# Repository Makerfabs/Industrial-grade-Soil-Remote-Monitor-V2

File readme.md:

# Makerfas Industrial-grade Soil Remote Monitor V2

```c++
/*
Version:		V1.1
Author:			Vincent
Create Date:	2023/7/25
Note:

*/
```

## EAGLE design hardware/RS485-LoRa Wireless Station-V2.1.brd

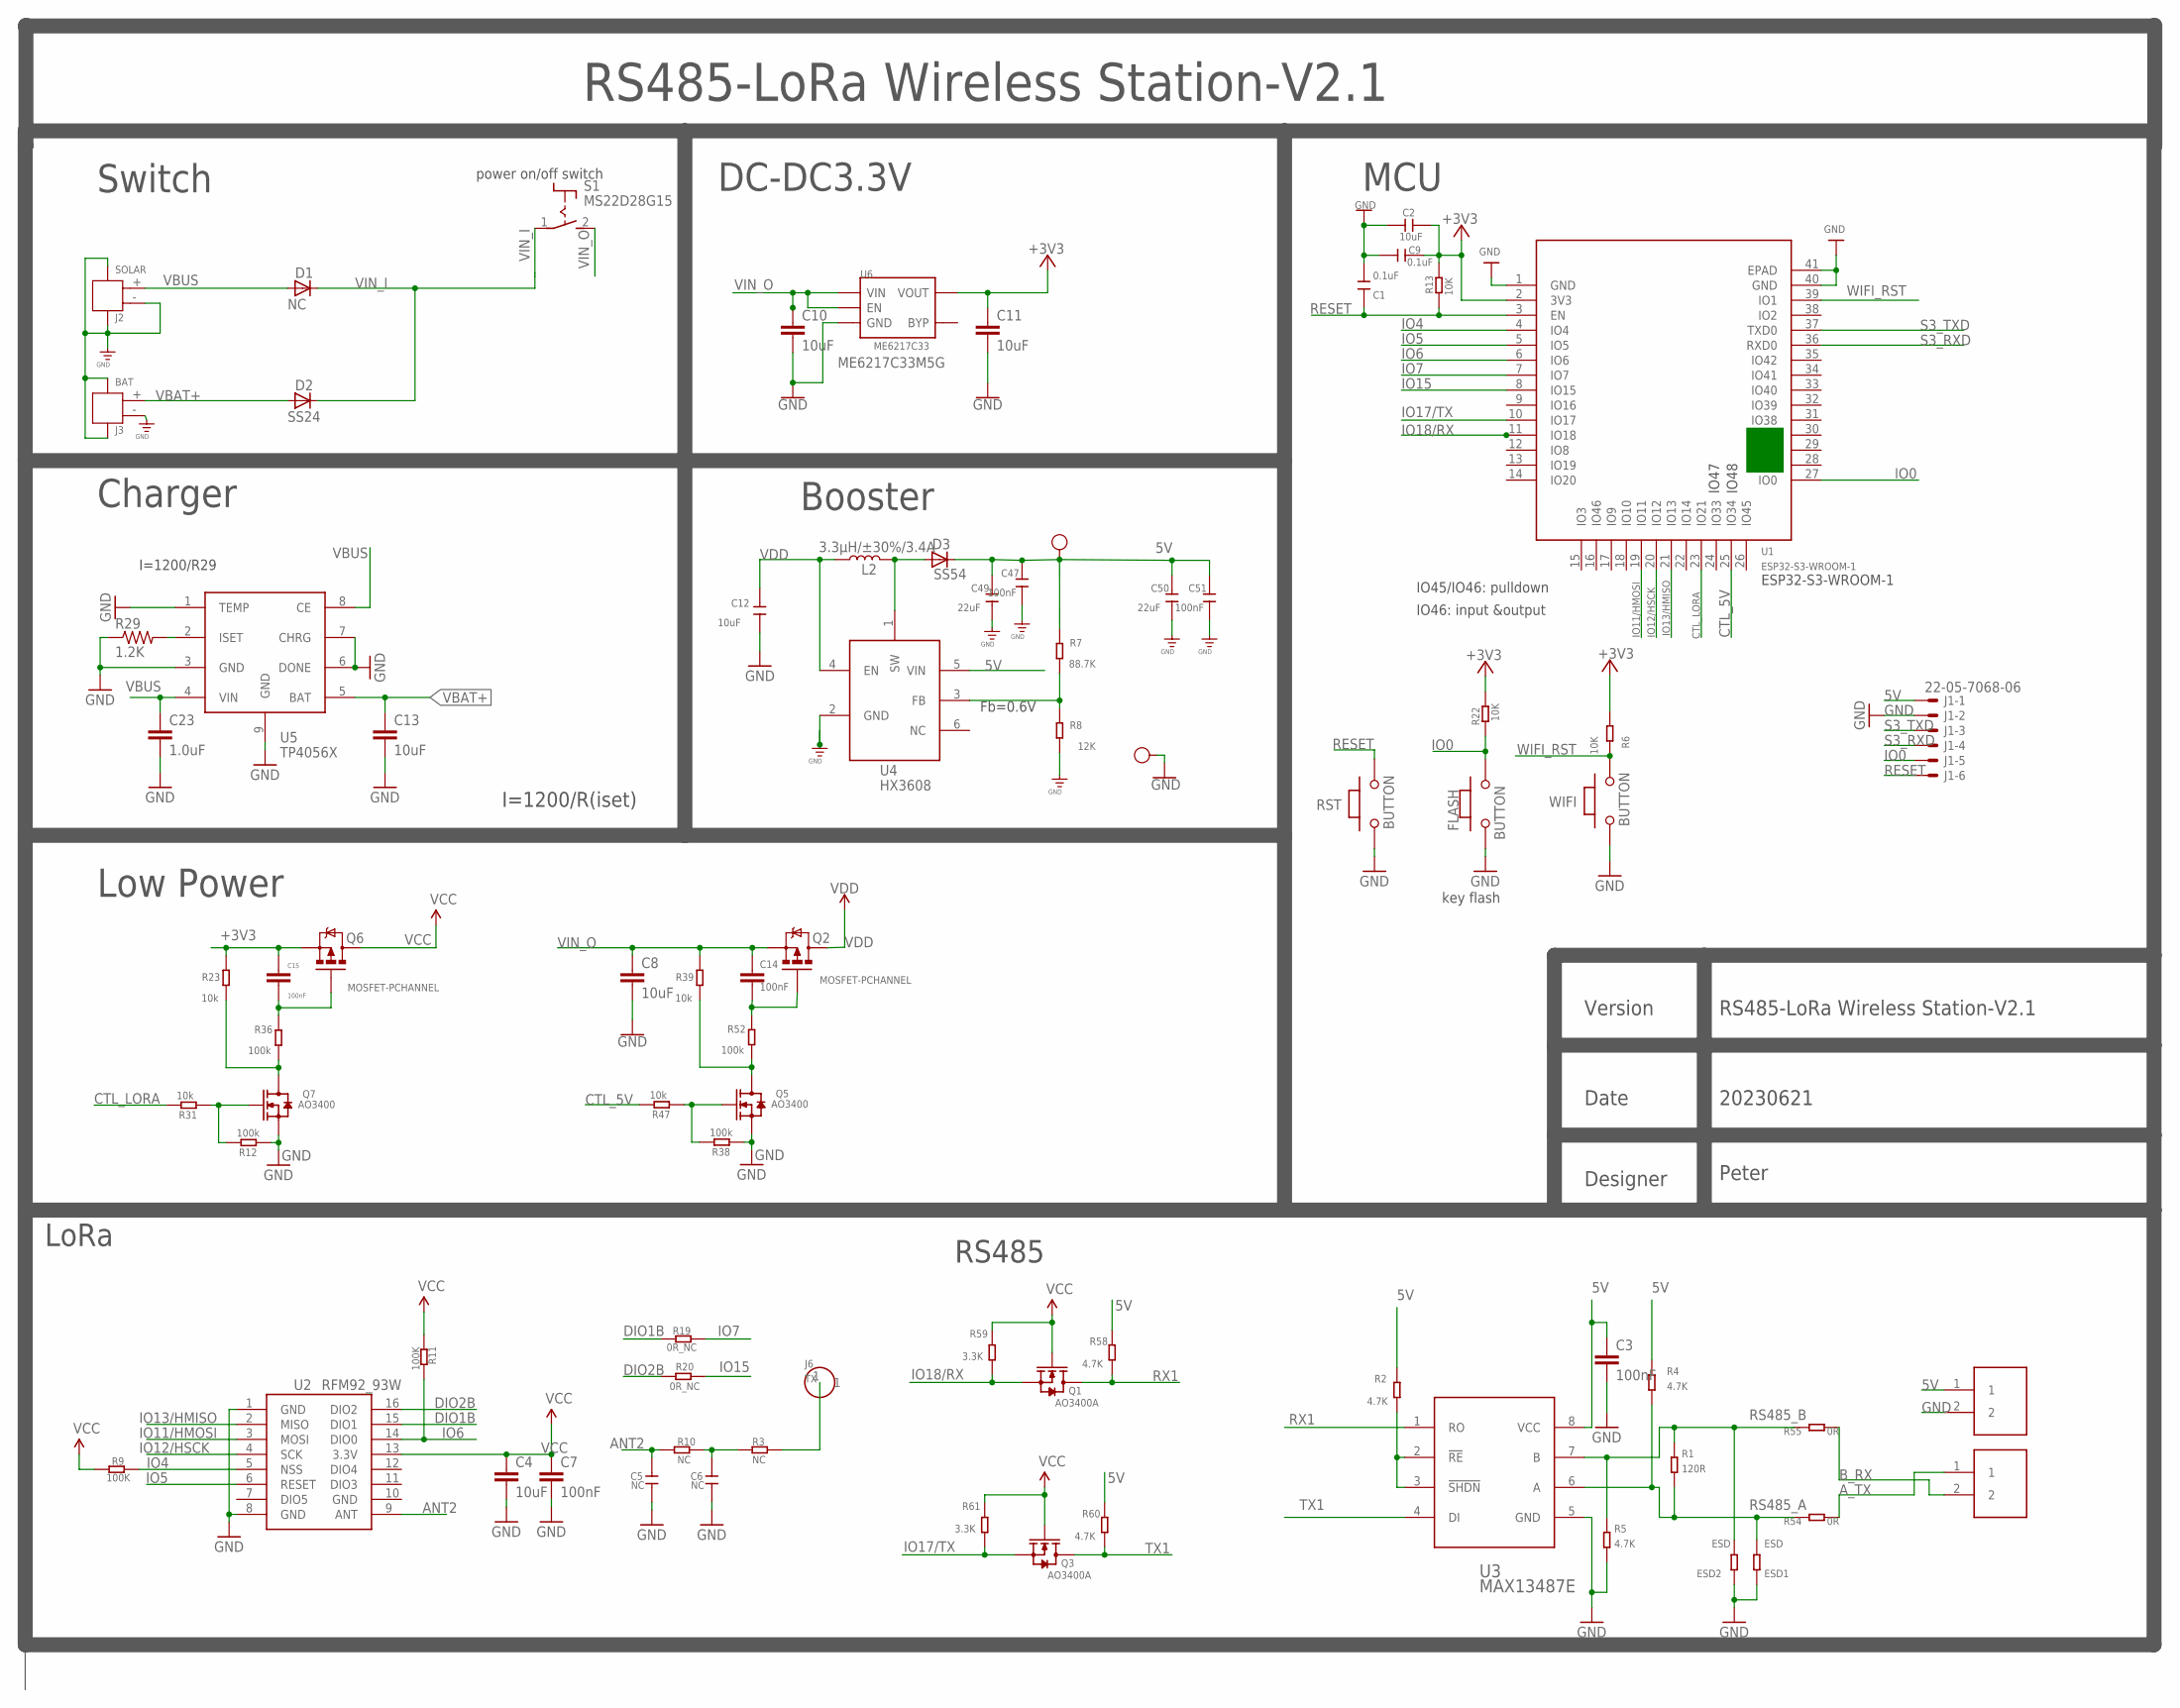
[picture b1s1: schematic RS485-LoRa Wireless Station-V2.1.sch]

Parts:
5V: HP; TP-D45MIL
C1, C9: 0.1uF; DISCRETE_C0603
C2: 10uF; DISCRETE_C0603
C3, C7, C14, C15, C47, C51: 100nF; C0603
C4, C8, C10, C11, C12, C13: 10uF; C0603
C5, C6: NC; DISCRETE_C0603
C23: 1.0uF; C0603
C49, C50: 22uF; C0603
D1: NC; DO-214AC
D2: SS24; DO-214AC
D3: SS54; DO-214AC
ESD1, ESD2: ESD; R0603
FLASH: BUTTON; 157SW
GND: HP; TP-D45MIL
J1: 22-05-7068-06; 7395-06
J2: SOLAR; HW2-SMD-2.0-90D
J3: BAT; HW2-SMD-2.0-90D
J4, J5: PH2.0-2P-DIP; PH2.0*2-DIP
J6: TX; 1P-100/50MIL
L2: 3.3µH/±30%/3.4A; CR54
Q1, Q3: AO3400A; SOT-23
Q2, Q6: MOSFET-PCHANNEL; SOT23-3
Q5, Q7: AO3400; SOT23@1
R1: 120R; R0603
R2, R4, R5, R58, R60: 4.7K; R0603
R3, R10: NC; DISCRETE_R0603
R6, R13, R22: 10K; R0603
R7: 88.7K; R0603
R8: 12K; R0603
R9, R11: 100K; R0603
R12, R36, R38, R52: 100k; R0603
R19, R20: 0R_NC; R0603
R23, R31, R39, R47: 10k; R0603
R29: 1.2K; R0603
R54, R55: 0R; R0603
R59, R61: 3.3K; R0603
RST: BUTTON; 157SW
S1: MS22D28G15; S-MS22D28G15
U1: ESP32-S3-WROOM-1; ESP32-­S2-­SOLO
U2: RFM92_93W
U3: MAX13487E; DIP8_MAX13487
U4: HX3608; SOT-23-6
U5: TP4056X; SOP8-1.27P
U6: ME6217C33; SOT23-5
WIFI: BUTTON; 157SW

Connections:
5V: 5V.T, C3.1, C47.1, C49.1, C50.1, C51.1, D3.C, J1.1, J4.1, R2.2, R4.2, R7.2, R58.2, R60.2, U3.8 (VCC), U4.5 (VIN)
+3V3: C2.1, C9.1, C11.1, C15.1, Q6.2 (S), R6.2, R13.2, R22.2, R23.2, U1.2 (3V3), U6.5 (VOUT)
ANT2: C5.2, R10.1, U2.9 (ANT)
A_TX: J5.1, R54.1
B_RX: J5.2, R55.1
CTL_5V: R47.2, U1.25 (IO34)
CTL_LORA: R31.2, U1.23 (IO21)
DIO1B: R19.2, U2.15 (DIO1)
DIO2B: R20.2, U2.16 (DIO2)
GND: C1.2, C2.2, C3.2, C4.2, C5.1, C6.1, C7.2, C8.2, C9.2, C10.2, C11.2, C12.2, C13.2, C23.2, C47.2, C49.2, C50.2, C51.2, ESD1.1, ESD2.1, FLASH.1, GND.T, J1.2, J2.3, J2.4, J2.- (2), J3.3, J3.4, J3.- (2), J4.2, Q5.2 (S), Q7.2 (S), R5.1, R8.1, R12.1, R29.1, R38.1, RST.1, U1.1 (GND), U1.40 (GND), U1.41 (EPAD), U2.1 (GND), U2.8 (GND), U2.10 (GND), U3.5 (GND), U4.2 (GND), U5.1 (TEMP), U5.3 (GND), U5.6 (DONE), U5.7 (CHRG), U5.9 (GND), U6.2 (GND), WIFI.1
IO0: FLASH.2, J1.5, R22.1, U1.27 (IO0)
IO4: R9.1, U1.4 (IO4), U2.5 (NSS)
IO5: U1.5 (IO5), U2.6 (RESET)
IO6: R11.1, U1.6 (IO6), U2.14 (DIO0)
IO7: R19.1, U1.7 (IO7)
IO11/HMOSI: U1.19 (IO11), U2.3 (MOSI)
IO12/HSCK: U1.20 (IO12), U2.4 (SCK)
IO13/HMISO: U1.21 (IO13), U2.2 (MISO)
IO15: R20.1, U1.8 (IO15)
IO17/TX: Q3.2 (S), R61.1, U1.10 (IO17)
IO18/RX: Q1.2 (S), R59.1, U1.11 (IO18)
ISET: R29.2, U5.2 (ISET)
unnamed: C6.2, R3.1, R10.2
unnamed: J6.1, R3.2
unnamed: C14.2, Q2.1 (G), R52.2
unnamed: Q5.1 (G), R38.2, R47.1
unnamed: C15.2, Q6.1 (G), R36.2
unnamed: Q7.1 (G), R12.2, R31.1
unnamed: Q7.3 (D), R23.1, R36.1
unnamed: D3.A, L2.P$2 (2), U4.1 (SW)
unnamed: R7.1, R8.2, U4.3 (FB)
unnamed: Q5.3 (D), R39.1, R52.1
unnamed: R2.1, U3.2 (!RE), U3.3 (!SHDN)
RESET: C1.1, J1.6, R13.1, RST.2, U1.3 (EN)
RS485_A: ESD1.2, R1.1, R4.1, R54.2, U3.6 (A)
RS485_B: ESD2.2, R1.2, R5.2, R55.2, U3.7 (B)
RX1: Q1.3 (D), R58.1, U3.1 (RO)
S3_RXD: J1.4, U1.36 (RXD0)
S3_TXD: J1.3, U1.37 (TXD0)
TX1: Q3.3 (D), R60.1, U3.4 (DI)
VBAT+: C13.1, D2.A, J3.+ (1), U5.5 (BAT)
VBUS: C23.1, D1.A, J2.+ (1), U5.4 (VIN), U5.8 (CE)
VCC: C4.1, C7.1, Q1.1 (G), Q3.1 (G), Q6.3 (D), R9.2, R11.2, R59.2, R61.2, U2.13 (3.3V)
VDD: C12.1, L2.P$1 (1), Q2.3 (D), U4.4 (EN)
VIN_I: D1.C, D2.C, S1.1
VIN_O: C8.1, C10.1, C14.1, Q2.2 (S), R39.2, S1.2 (S), U6.1 (VIN), U6.3 (EN)
WIFI_RST: R6.1, U1.39 (IO1), WIFI.2

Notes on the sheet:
DC-DC3.3V
I=1200/R29
ME6217C33M5G
Fb=0.6V
Charger
Booster
LoRa
RS485
power on/off switch
key flash
Switch
MCU
Low Power
IO45/IO46: pulldown
IO46: input &output
ESP32-S3-WROOM-1
IO47
IO48
I=1200/R(iset)
Version
Date
Designer
RS485-LoRa Wireless Station-V2.1
20230621
Peter

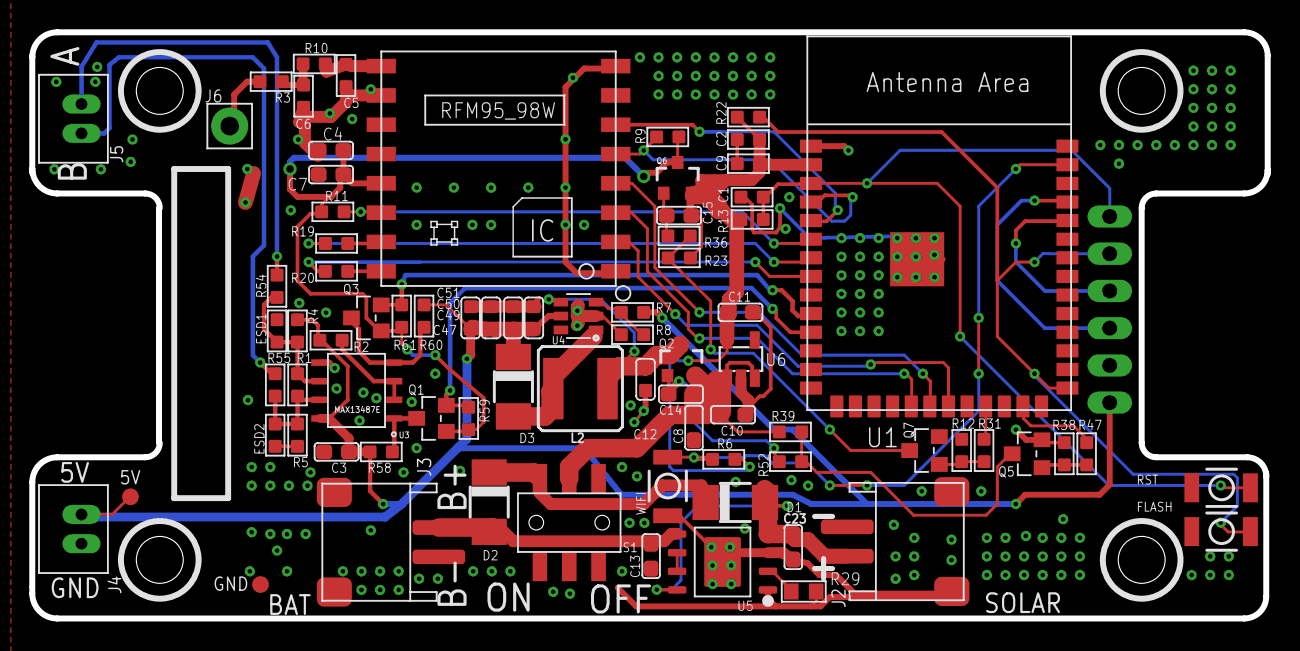
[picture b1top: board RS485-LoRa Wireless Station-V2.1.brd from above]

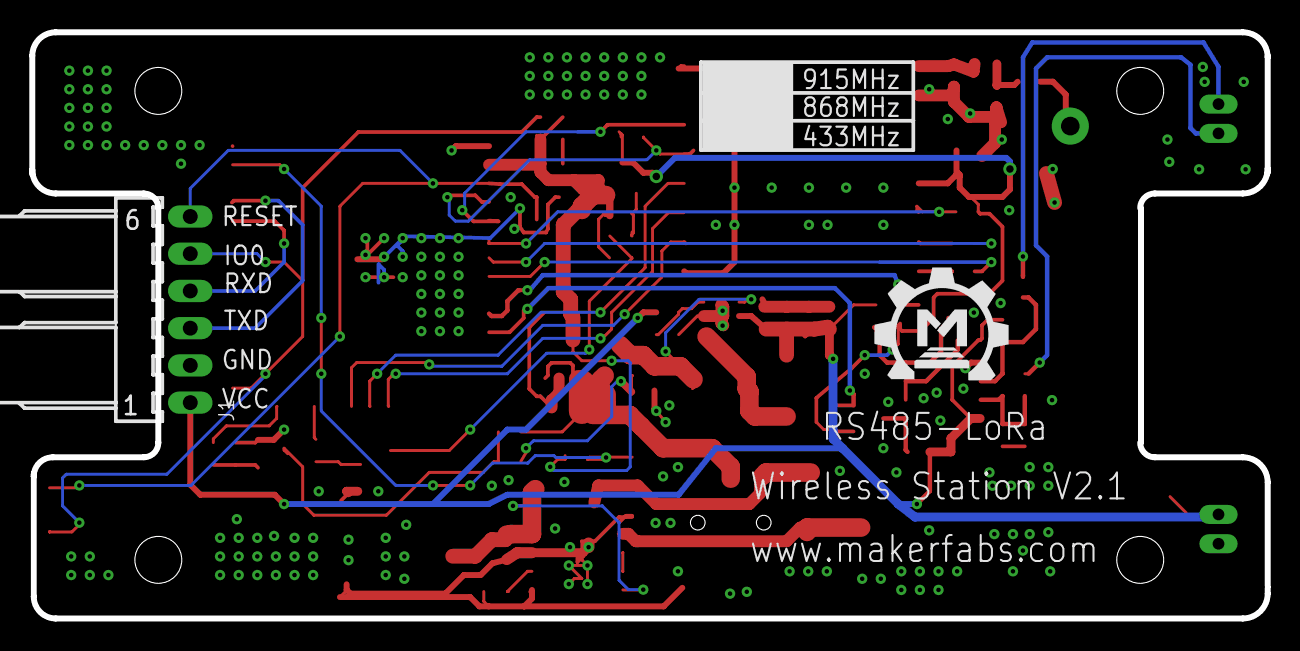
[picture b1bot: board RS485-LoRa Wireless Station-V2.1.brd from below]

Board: 2 copper layers, 84.3 x 40.0 mm, 81 parts (2 on the bottom side), 47 nets.

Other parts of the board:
U$3: MAKERFABS_0.3

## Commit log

2023-06-29 Create
2023-06-30 Add tft receiver
2023-06-30 Update hardware
2023-06-30 Fix bug
2023-07-06 Edit ap name
2023-07-25 test
2023-07-25 change to new file
2023-07-25 new arduino file without N/P/K
2023-07-25 V1.1
2023-07-25 V 1.1
2023-09-16 Firmware V1.1
2023-09-16 Change lora data format
2024-03-12 Add 915 Version
2024-06-27 Add battery detect

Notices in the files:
parts and their libraries:
User-Submitted: Licensing: Creative Commons ShareAlike 4.0 International - https://creativecommons.org/licenses/by-sa/4.0
microbuilder: This work is placed in the public domain, and may be freely used for commercial and non-commercial work with the following conditions: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
